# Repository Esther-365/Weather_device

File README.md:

# Weather_device

A smart weather hardware inspired that meshtimes, that displays current weather conditions, time, and gives outfit recommendations. It connects to Wi-Fi, gets weather information from an online weather service, and displays it on a color TFT screen. It also has a pixel-art teddy bear, weather-themed music, and a button for controlling the audio.

**Components**
1. Seeed Studio XIAO ESP32-S3 - Connects to WiFi and gets HTTP response from Open Meteo
2. NS4168 I2S Audio Amplifier & 3W Speaker Kit - Plays sound based on weather.
3. 2.0inch SPI LCD TFT Display - Displays weather and outfit recommendations.

*Bill Of Materials (BOM)* 
| Part | Description | Qty | Unit Price | Total | Vendor |
|------|-------------|----:|-----------:|------:|-------------|
| XIAO ESP32-S3 (7.05) | MicroController | 1 | $7.49 | $7.49 | https://www.seeedstudio.com/XIAO-ESP32S3-p-5627.html |
| 2.0inch SPI LCD TFT Display | For display | 1 | $8.99 | $8.99 | https://www.amazon.com/dp/B0H8RNZY9M|
| 2.5mm 8 pin female header socket | Connects screen to PCB | 1 | $5.99 | $5.99 | https://www.amazon.com/dp/B0F3CXRDF3 |
| NS4168 I2S Audio Amplifier & 3W Speaker Kit | Plays sound | 1 | $9.99 | $9.99 | https://www.amazon.com/dp/B0GV33LRR5 |
| Male Header Pin 2.54 mm | Connects amplifier to PCB | 1 | $6.98 | $6.98 | https://www.amazon.com/dp/B0FLJVHSRN |
| PCB | Host all components | 1 | $10.00 | $10.00 | https://jlcpcb.com/quote |

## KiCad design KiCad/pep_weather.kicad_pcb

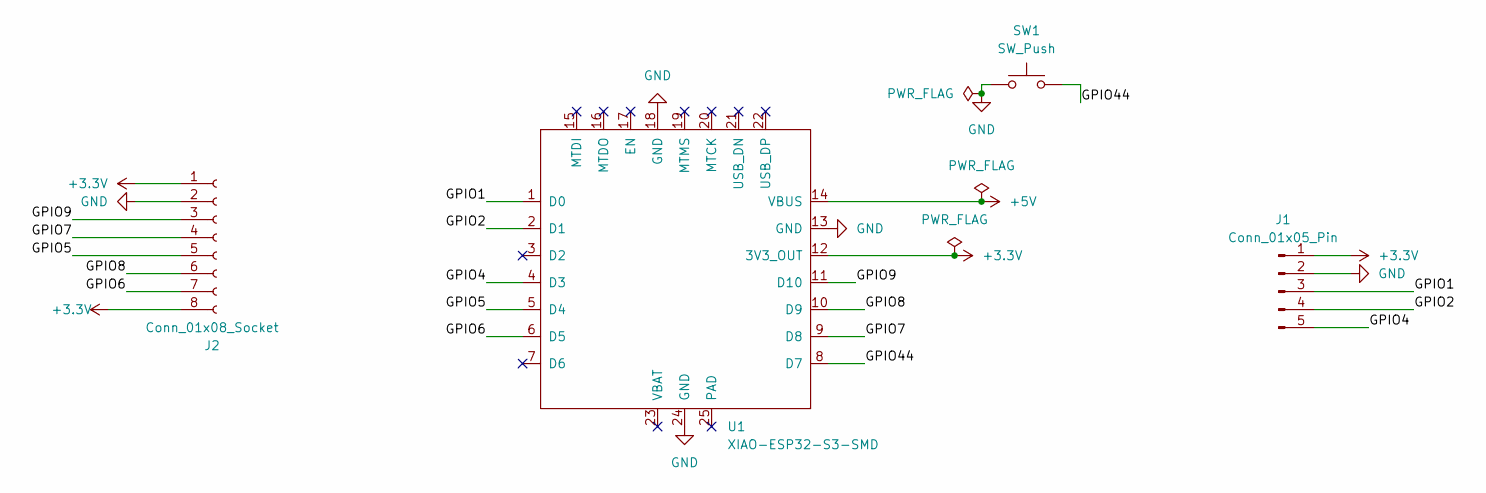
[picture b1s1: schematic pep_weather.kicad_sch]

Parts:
J1: Conn_01x05_Pin; PinHeader_1x05_P2.54mm_Vertical
J2: Conn_01x08_Socket; PinSocket_1x08_P2.54mm_Vertical
SW1: SW_Push; SW_Cherry_MX_1.00u_PCB
U1: XIAO-ESP32-S3-SMD

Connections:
+3.3V: J1.1, J2.1, J2.8, U1.12 (3V3_OUT)
+5V: U1.14 (VBUS)
/GPIO1: J1.3, U1.1 (D0)
/GPIO2: J1.4, U1.2 (D1)
/GPIO4: J1.5, U1.4 (D3)
/GPIO5: J2.5, U1.5 (D4)
/GPIO6: J2.7, U1.6 (D5)
/GPIO7: J2.4, U1.9 (D8)
/GPIO8: J2.6, U1.10 (D9)
/GPIO9: J2.3, U1.11 (D10)
/GPIO44: SW1.2, U1.8 (D7)
GND: J1.2, J2.2, SW1.1, U1.13 (GND), U1.18 (GND), U1.24 (GND)

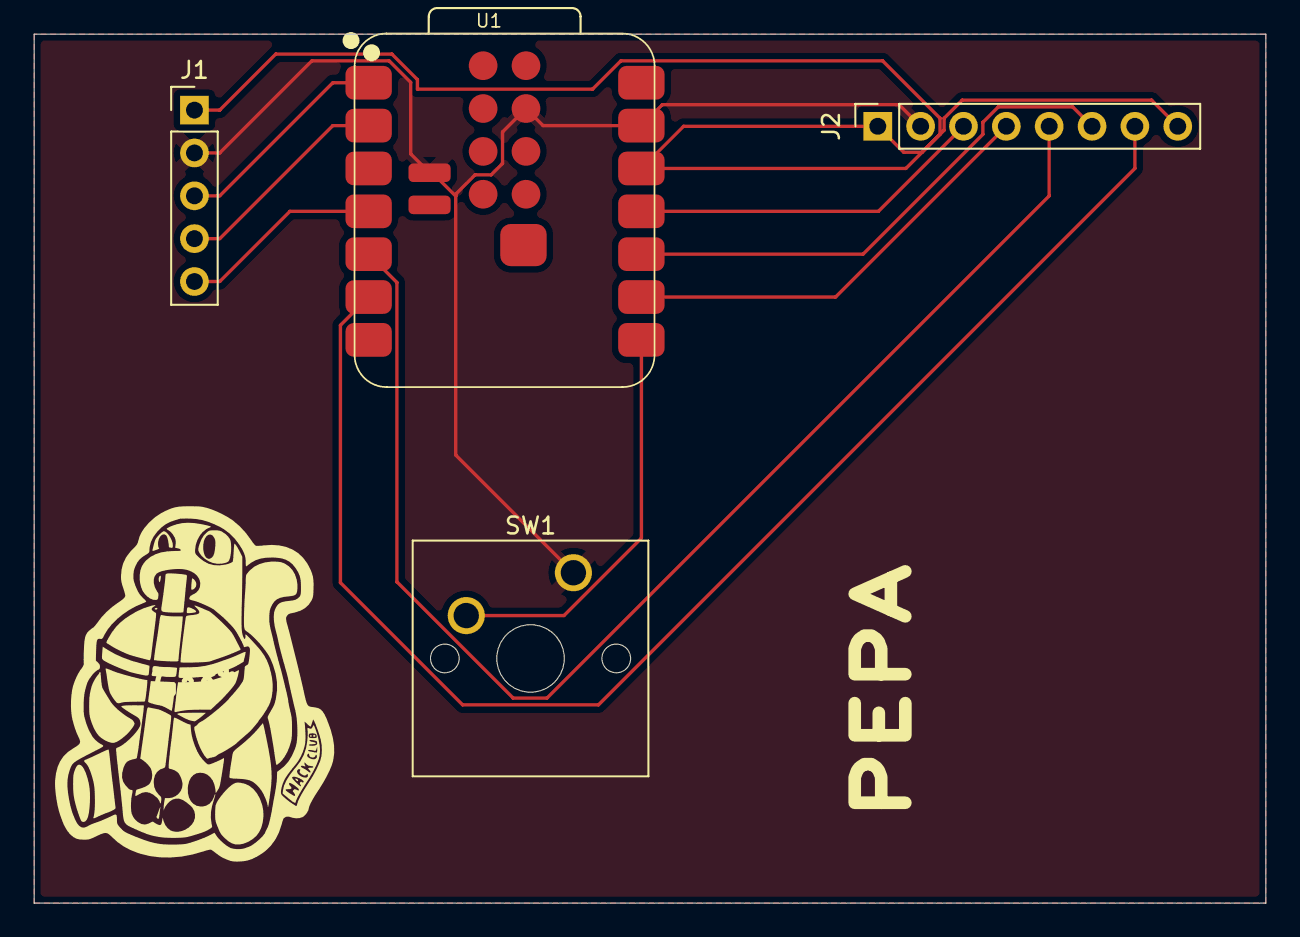
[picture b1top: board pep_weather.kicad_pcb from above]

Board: 2 copper layers, 73.0 x 51.5 mm, 4 parts (0 on the bottom side), 11 nets.
